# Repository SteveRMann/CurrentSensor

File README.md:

## **Current Sensor**

### **What is the Current Sensor for?**

The current sensor is designed to provide feedback via mqtt status messages for devices that have
no such ability.
For example, if the television is controlled by an mqtt relay, there is no status message telling the 
controller if the TV is on or off in the first place.

### **How to use it**
There is a sense wire on the PCB. This sense wire is to be placed around or adjacent to the "live" side
of the power cable to the device.  When properly placed, the LED on the board will turn on or off as the
power to the device is turned on or off.

#### **`Acknowledgements`**
This project was inspired by a You Tube video by Ralph Bacon:
'No contact mains detector for Arduino & Pi'.
https://www.youtube.com/watch?v=cDuObAR42Nw

I simply put his circuit on a PCB, added an ESP8266-01 and the Arduino code.

##**The remainder is for appearance experiments only**

CA3046
TPQ3904

```Arduino
#include <EEPROM.h>

void setup(){

}

void loop(){

}

```

The library provides a global variable named `EEPROM`, you use this variable to access the library functions. The methods provided in the EEPROM class are listed below.

You can view all the examples [here](examples/).

### **Library functions**

#### **`EEPROM.read( address )`** [[_example_]](examples/eeprom_read/eeprom_read.ino)

This function allows you to read a single byte of data from the eeprom.
Its only parameter is an `int` which should be set to the address you wish to read.

The function returns an `unsigned char` containing the value read.

#### **`EEPROM.write( address, value )`** [[_example_]](examples/eeprom_write/eeprom_write.ino)

The `write()` method allows you to write a single byte of data to the EEPROM.
Two parameters are needed. The first is an `int` containing the address that is to be written, and the second is a the data to be written (`unsigned char`).

This function does not return any value.

#### **`EEPROM.update( address, value )`** [[_example_]](examples/eeprom_update/eeprom_update.ino)

This function is similar to `EEPROM.write()` however this method will only write data if the cell contents pointed to by `address` is different to `value`. This method can help prevent unnecessary wear on the EEPROM cells.

This function does not return any value.

#### **`EEPROM.get( address, object )`** [[_example_]](examples/eeprom_get/eeprom_get.ino)

This function will retrieve any object from the EEPROM.
Two parameters are needed to call this function. The first is an `int` containing the address that is to be written, and the second is the object you would like to read.

This function returns a reference to the `object` passed in. It does not need to be used and is only returned for conveience.

#### **`EEPROM.put( address, object )`** [[_example_]](examples/eeprom_put/eeprom_put.ino)

This function will write any object to the EEPROM.
Two parameters are needed to call this function. The first is an `int` containing the address that is to be written, and the second is the object you would like to write.

This function uses the _update_ method to write its data, and therefore only rewrites changed cells.

This function returns a reference to the `object` passed in. It does not need to be used and is only returned for conveience.

#### **Subscript operator: `EEPROM[address]`** [[_example_]](examples/eeprom_crc/eeprom_crc.ino)

This operator allows using the identifier `EEPROM` like an array.  
EEPROM cells can be read _and_ **_written_** directly using this method.

This operator returns a reference to the EEPROM cell.

```c++
unsigned char val;

//Read first EEPROM cell.
val = EEPROM[ 0 ];

//Write first EEPROM cell.
EEPROM[ 0 ] = val;

//Compare contents
if( val == EEPROM[ 0 ] ){
  //Do something...
}
```

#### **`EEPROM.length()`**

This function returns an `unsigned int` containing the number of cells in the EEPROM.

---

### **Advanced features**

This library uses a component based approach to provide its functionality. This means you can also use these components to design a customized approach. Two background classes are available for use: `EERef` & `EEPtr`.

#### **`EERef` class**

This object references an EEPROM cell.
Its purpose is to mimic a typical byte of RAM, however its storage is the EEPROM.
This class has an overhead of two bytes, similar to storing a pointer to an EEPROM cell.

```C++
EERef ref = EEPROM[ 10 ]; //Create a reference to 11th cell.

ref = 4; //write to EEPROM cell.

unsigned char val = ref; //Read referenced cell.
```

#### **`EEPtr` class**

This object is a bidirectional pointer to EEPROM cells represented by `EERef` objects.
Just like a normal pointer type, this type can be dereferenced and repositioned using 
increment/decrement operators.

```C++
EEPtr ptr = 10; //Create a pointer to 11th cell.

*ptr = 4; //dereference and write to EEPROM cell.

unsigned char val = *ptr; //dereference and read.

ptr++; //Move to next EEPROM cell.
```

#### **`EEPROM.begin()`**

This function returns an `EEPtr` pointing to the first cell in the EEPROM.  
This is useful for STL objects, custom iteration and C++11 style ranged for loops.

#### **`EEPROM.end()`**

This function returns an `EEPtr` pointing at the location after the last EEPROM cell.  
Used with `begin()` to provide custom iteration.

**Note:** The `EEPtr` returned is invalid as it is out of range. Infact the hardware causes wrapping of the address (overflow) and `EEPROM.end()` actually references the first EEPROM cell.

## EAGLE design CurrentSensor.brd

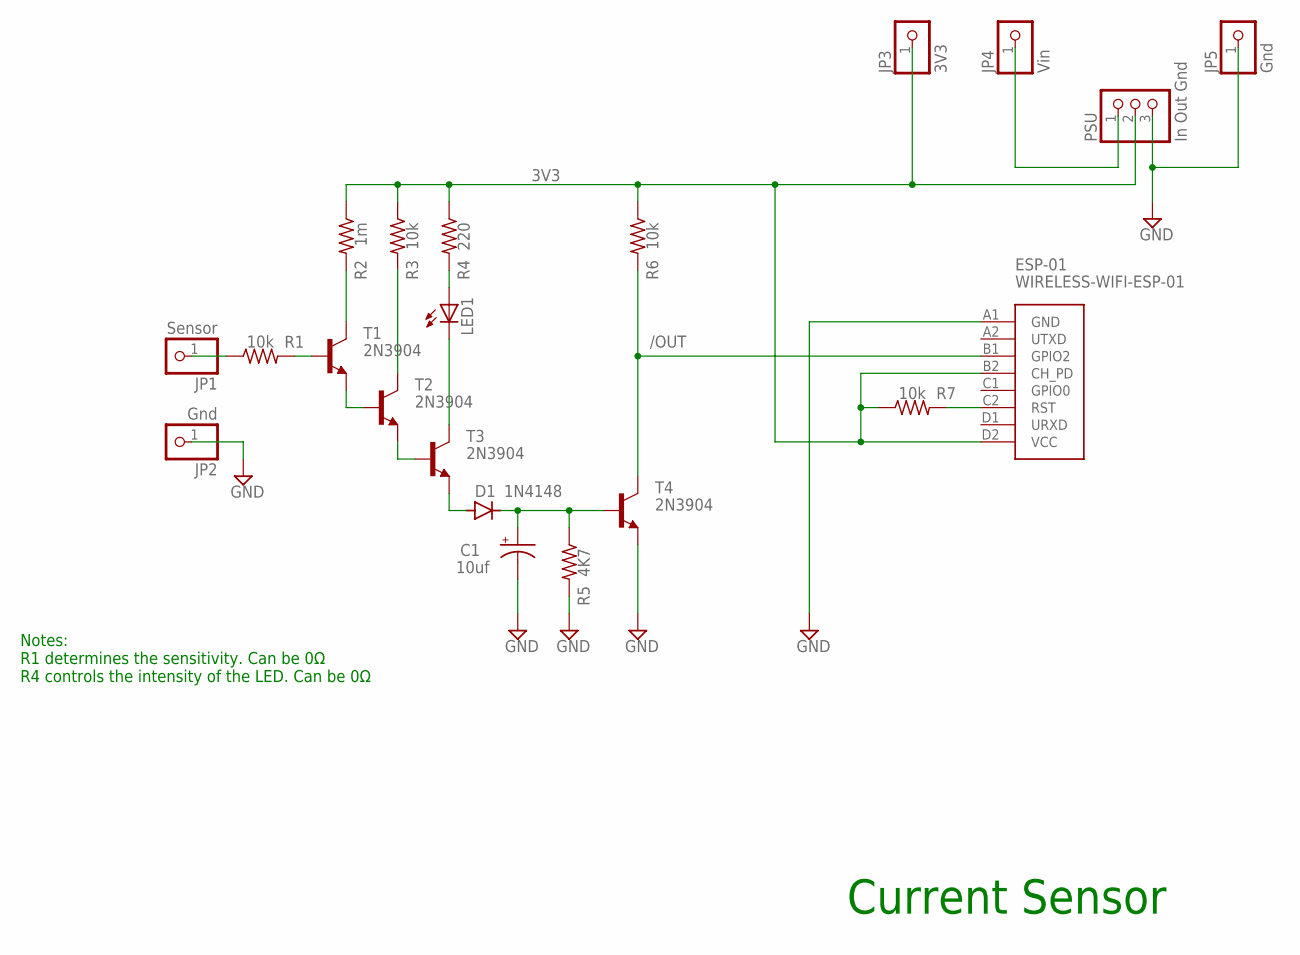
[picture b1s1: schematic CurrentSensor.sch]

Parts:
C1: 10uf; E15-5
D1: 1N4148; DO35-10
ESP-01: WIRELESS-WIFI-ESP-01
JP1: Sensor; 1X01
JP2: Gnd; 1X01
JP3: 3V3; 1X01-CLEANBIG
JP4: Vin; 1X01-CLEANBIG
JP5: Gnd; 1X01-CLEANBIG
LED1: LED5MM
PSU: In Out Gnd; 1X03-CLEANBIG
R1, R3, R6, R7: 10k; 0207/9
R2: 1m; 0207/9
R4: 220; 0207/9
R5: 4K7; 0207/9
T1, T2, T3, T4: 2N3904; TO92

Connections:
3V3: ESP-01.B2 (CH_PD), ESP-01.D2 (VCC), JP3.1, PSU.2, R2.1, R3.1, R4.1, R6.1, R7.1
/OUT: ESP-01.B1 (GPIO2), R6.2, T4.1 (C)
GND: C1.-, ESP-01.A1 (GND), JP2.1, JP5.1, PSU.3, R5.2, T4.3 (E)
unnamed: JP4.1, PSU.1
unnamed: JP1.1, R1.1
unnamed: T1.3 (E), T2.2 (B)
unnamed: T2.3 (E), T3.2 (B)
unnamed: D1.A, T3.3 (E)
unnamed: C1.+, D1.C, R5.1, T4.2 (B)
unnamed: LED1.K (C), T3.1 (C)
unnamed: LED1.A, R4.2
unnamed: R3.2, T2.1 (C)
unnamed: R2.2, T1.1 (C)
unnamed: R1.2, T1.2 (B)
unnamed: ESP-01.C2 (RST), R7.2

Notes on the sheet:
Current Sensor
Notes: R1 determines the sensitivity. Can be 0Ω R4 controls the intensity of the LED. Can be 0Ω

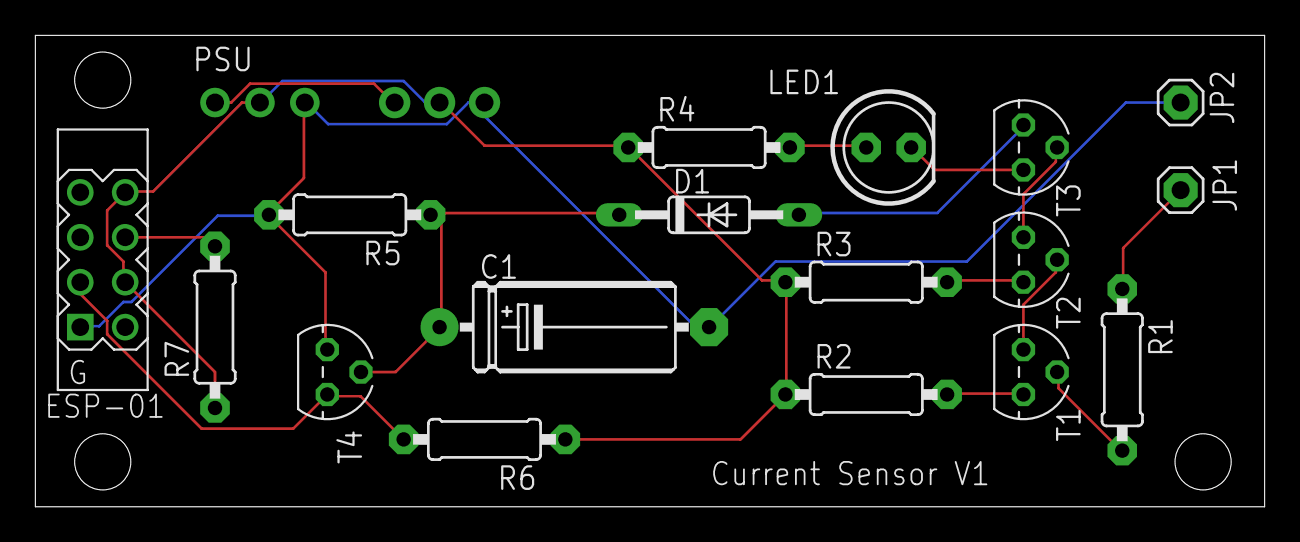
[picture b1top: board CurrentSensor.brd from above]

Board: 2 copper layers, 69.5 x 26.7 mm, 21 parts (0 on the bottom side), 15 nets.

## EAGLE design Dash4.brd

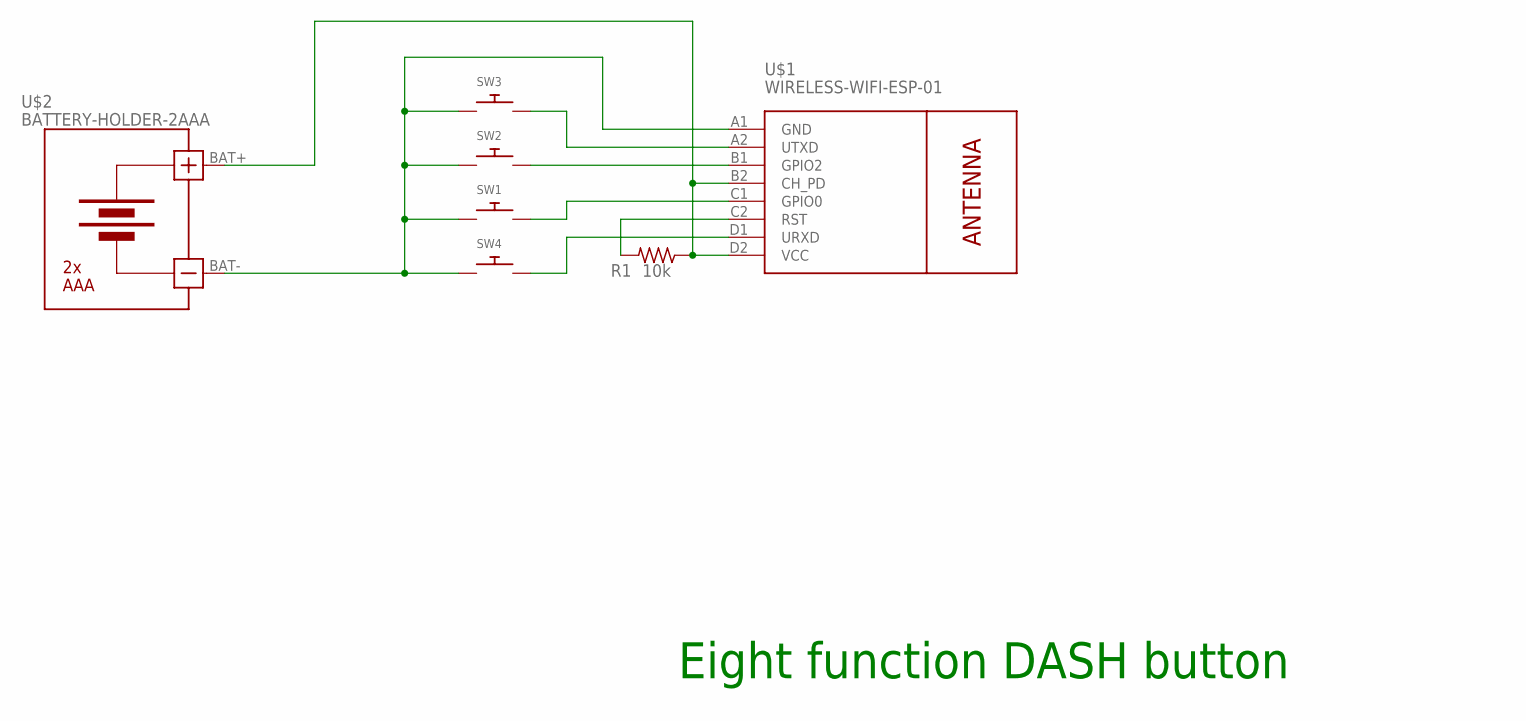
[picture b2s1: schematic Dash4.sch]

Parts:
R1: 10k; 0207/9
SW1, SW2, SW3, SW4: SWITCH_PUSHBUTTONEVQ-PE; TACT_PANA-EVQ
U$1: WIRELESS-WIFI-ESP-01
U$2: BATTERY-HOLDER-2AAA

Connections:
unnamed: SW4.P$2, U$1.D1 (URXD)
unnamed: R1.1, U$1.B2 (CH_PD), U$1.D2 (VCC), U$2.BAT+
unnamed: R1.2, U$1.C2 (RST)
unnamed: SW1.P$2, U$1.C1 (GPIO0)
unnamed: SW2.P$2, U$1.B1 (GPIO2)
unnamed: SW3.P$2, U$1.A2 (UTXD)
unnamed: SW1.P$1, SW2.P$1, SW3.P$1, SW4.P$1, U$1.A1 (GND), U$2.BAT-

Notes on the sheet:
Eight function DASH button

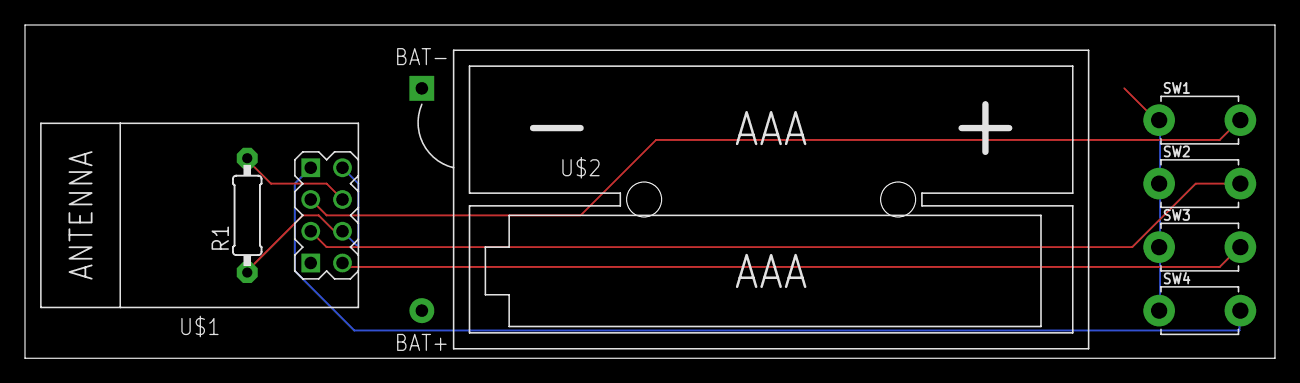
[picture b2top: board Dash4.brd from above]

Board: 2 copper layers, 100.0 x 26.7 mm, 7 parts (0 on the bottom side), 7 nets.

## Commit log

2020-06-22 Initial upload
2020-06-29 Added LED on GPIO2
    The function blinkLed() switches pin2 mode to output, flashes the LED then sets the pinmode back to input.
2020-06-29 Removed LED
2020-06-29 Removed calls to blinkLed()
2020-06-30 Added GPIO pinout drawing, cleaned up schematic
2020-06-30 Annotated schematic
2020-06-30 Removed all references to LED
2020-07-09 Initial files
2020-07-16 Add files via upload
    Added an on-board regulator.

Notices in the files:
parts and their libraries:
diy-modules: Released under the Creative Commons Attribution 4.0 International License: http://creativecommons.org/licenses/by/4.0
